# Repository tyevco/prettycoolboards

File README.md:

# prettycoolboards

**Docs site:** <https://tyevco.github.io/prettycoolboards/>

Open hardware boards designed as code. The schematics and PCBs are generated
from Python into KiCad 10, routed with Freerouting plus a grid router, and
gated by ERC, DRC and schematic parity before any fab output is written.
Enclosures and mechanics are in build123d.

## Boards

| Board | Status | |
|---|---|---|
| [PrettyCool Caliper](caliper/README.md) | rev A in design | 150 mm digital caliper: magnetic and capacitive sensing, ESP32-S3 with BLE + Wi-Fi, colour IPS, reading memory, go/no-go, USB-C |

## Repository layout

```
tools/        shared Python → KiCad generator toolchain (see tools/README.md)
caliper/      one folder per board: hardware/, firmware/, app/, docs/
.vitepress/   docs site (VitePress), published to GitHub Pages by .github/workflows/docs.yml
```

The hardware toolchain runs on Linux: KiCad 10 (`kicad-cli` + `pcbnew`), Java 21 +
Freerouting 2.1, ngspice and build123d. On Windows, run it in WSL.

```sh
npm ci && npm run docs:dev   # preview the docs site locally
```

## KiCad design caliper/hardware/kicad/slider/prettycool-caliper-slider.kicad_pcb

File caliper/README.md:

# PrettyCool Caliper

A 150 mm digital caliper that remembers its readings and sends them wirelessly.

> **Status (2026-11-10): rev A designed, not built.** Schematics captured (ERC clean, 2 waived); both boards laid
> out and routed (KiCad 10.0.8 DRC + schematic parity: 0 errors, 0 unconnected); both fab packages pass
> `release.py`, including the jlcplace placement gate (slider 107 rows, 0 red, 0 yellow); the mechanics pass the clash
> check against the routed board; the firmware builds for the ESP32-S3 and passes its host tests. Nothing has been
> fabricated, flashed, printed or measured, and no SPICE simulation has been run. Every figure here is a design
> target until the prototype passes [bring-up](docs/bringup.md).

| | |
|---|---|
| Sensing | AS5311 magnetic linear encoder over 2 mm-pole tape (0.488 µm internal resolution: the 1.95 µm quadrature count interpolated with the 12-bit SSI position), plus an experimental 8-phase capacitive scale on its own PCB, read side by side |
| Brains | ESP32-S3-MINI-1: BLE 5 and Wi-Fi |
| Display | 1.14 in colour IPS, landscape: big reading, live graph, go/no-go gauge, stats |
| Wireless | BLE HID keyboard (types the reading into any spreadsheet), a companion GATT app, a Wi-Fi web page, MQTT/HTTP push |
| Memory | Thousands of readings with timestamps and tolerance profiles; CSV export over USB, Wi-Fi or BLE |
| Smarts | Tolerance / go-no-go, min/max/mean/σ stats, 6-axis IMU (accelerometer + gyroscope): wake-on-pickup, auto-hold, orientation tracking; a compass (IIS2MDC magnetometer) as a reference that keeps the relative yaw from drifting: beside a steel beam it reads the local field, not north, and how well that works is unmeasured |
| Power | 135 mAh LiPo (501230 class, behind the board), USB-C charging (BQ25180), fuel gauge, buck-boost 3V3. Estimated ≈ 3 days per charge on a typical shop day (30 min measuring a day), ≈ 1 h 40 min of continuous measuring ([architecture §5](docs/architecture.md)); not measured |
| Body | Rev A: printed slider on a ground 20 × 4 mm flat-stock beam. Rev B: CNC-machined drawings. Slider housing 77 × 39 × 16 mm (slimmed from 77 × 52 × 16 on 2026-11-09) |

**[3D gallery](https://tyevco.github.io/prettycoolboards/caliper/gallery/):** rotate the assembly, the exploded
view, the housing on its own, the before/after slim-down and both circuit boards, plus the full render set.

## Documentation

| Document | Contents |
|---|---|
| [docs/architecture.md](docs/architecture.md) | System overview, decisions and the alternatives that were rejected, power budget |
| [hardware/design/SPEC.md](hardware/design/SPEC.md) | **Architecture of record**: boards, placement, power tree, pin map |
| [docs/electronics.md](docs/electronics.md) | Schematics, boards, ERC/DRC status, renders |
| [docs/mechanical.md](docs/mechanical.md) | Beam, slider housing, gibs, jaws; printed rev A and machined rev B |
| [docs/simulation.md](docs/simulation.md) | Placeholder: the SPICE checks of the power path and the capacitive front-end are not written or run yet |
| [docs/firmware.md](docs/firmware.md) | ESP-IDF firmware: sensing, UI, BLE, Wi-Fi, storage, power |
| [docs/app.md](docs/app.md) | Web Bluetooth companion page |
| [docs/assembly.md](docs/assembly.md) | Ordering (JLCPCB), sourcing, assembly |
| [docs/ordering.md](docs/ordering.md) | One-page order checklist: JLC options, panel, rough cost, off-board parts (prepared, nothing ordered) |
| [docs/bringup.md](docs/bringup.md) | The bring-up procedure B-0…B-17: test pads, supplies, meter points, expected values, the `bu` console checks; written, not run |

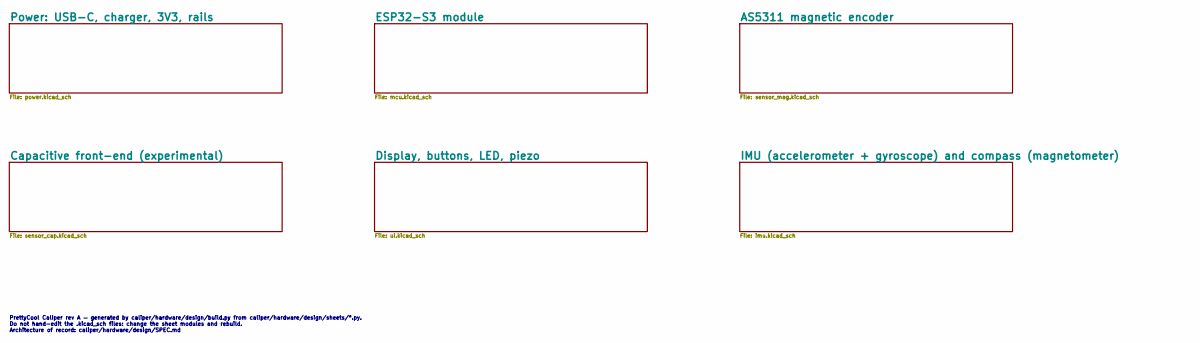
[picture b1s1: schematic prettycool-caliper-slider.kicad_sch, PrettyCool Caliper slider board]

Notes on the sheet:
PrettyCool Caliper rev A — generated by caliper/hardware/design/build.py from caliper/hardware/design/sheets/*.py. Do not hand-edit the .kicad_sch files: change the sheet modules and rebuild. Architecture of record: caliper/hardware/design/SPEC.md

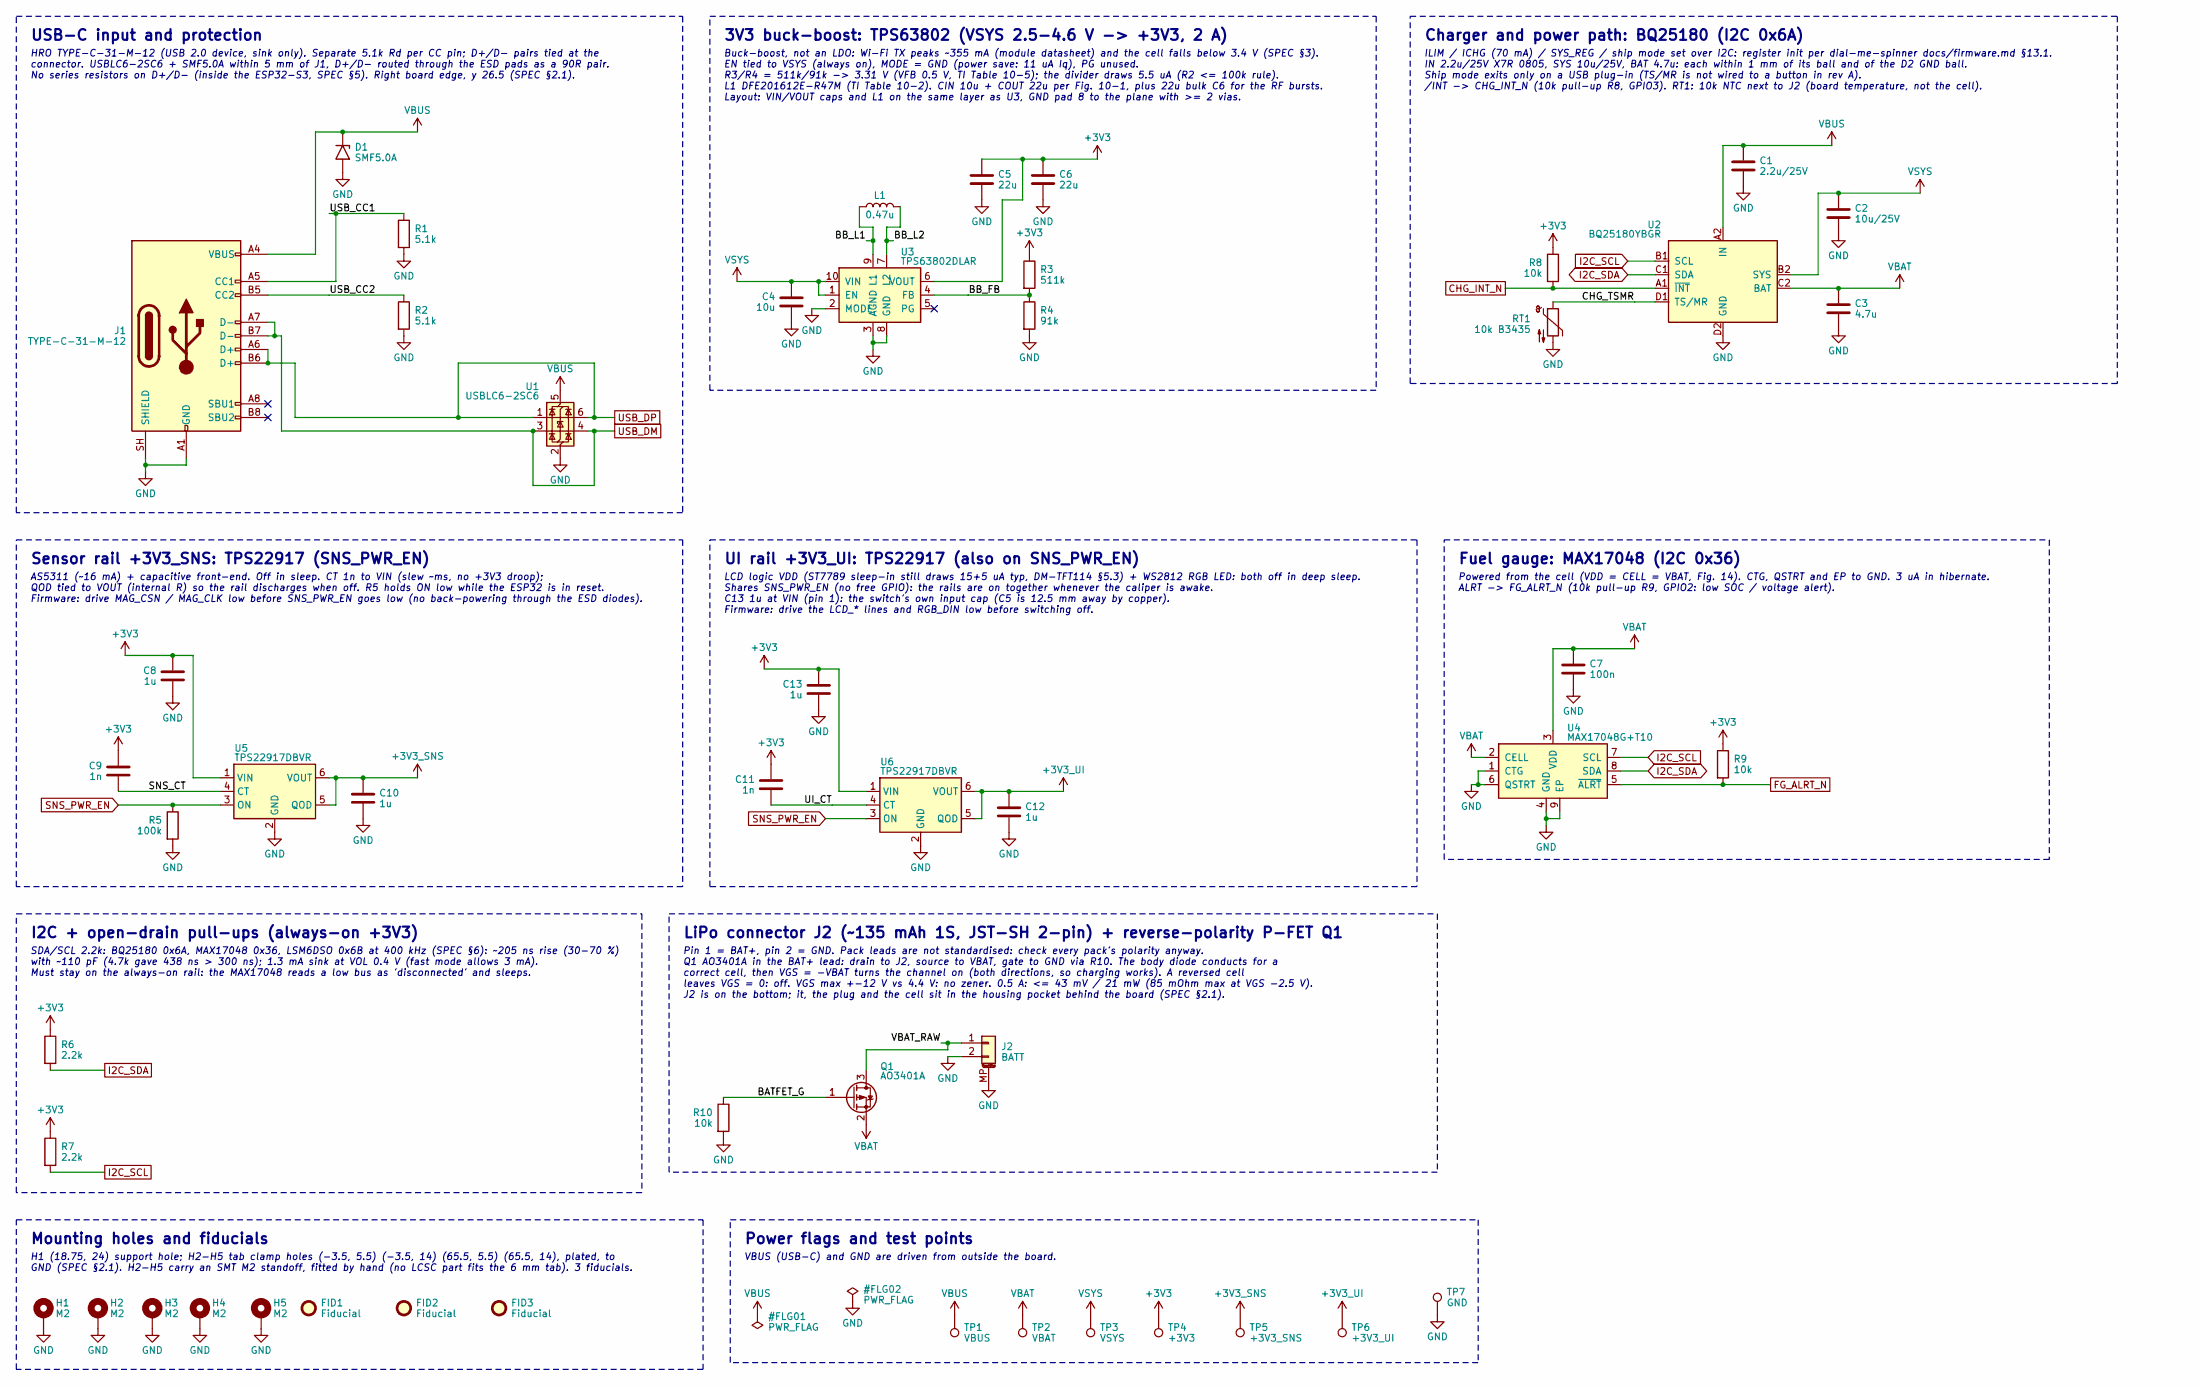
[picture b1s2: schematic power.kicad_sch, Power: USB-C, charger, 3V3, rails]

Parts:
C1: 2.2u/25V; C_0805_2012Metric; MPN CC0805KKX7R8BB225; LCSC C277470
C2: 10u/25V; C_0603_1608Metric; MPN CL10A106MA8NRNC; LCSC C96446
C3: 4.7u; C_0603_1608Metric; MPN CL10A475KO8NNNC; LCSC C19666
C4: 10u; C_0603_1608Metric; MPN CL10A106KP8NNNC; LCSC C19702
C5, C6: 22u; C_0603_1608Metric; MPN CL10A226MQ8NRNC; LCSC C59461
C7: 100n; C_0402_1005Metric; MPN CL05B104KO5NNNC; LCSC C1525
C8, C10, C12, C13: 1u; C_0402_1005Metric; MPN CL05A105KA5NQNC; LCSC C52923
C9, C11: 1n; C_0402_1005Metric; MPN 0402B102K500NT; LCSC C1523
D1: SMF5.0A; D_SMF; MPN SMF5.0A; LCSC C151296
FID1, FID2, FID3: Fiducial; Fiducial_1mm_Mask2mm
H1, H2, H3, H4, H5: M2; MountingHole_2.2mm_M2_Pad_Via
J1: TYPE-C-31-M-12; USB_C_Receptacle_HRO_TYPE-C-31-M-12; MPN TYPE-C-31-M-12; LCSC C165948
J2: BATT; JST_SH_SM02B-SRSS-TB_1x02-1MP_P1.00mm_Horizontal; MPN SM02B-SRSS-TB(LF)(SN); LCSC C160402
L1: 0.47u; L_Murata_DFE201610P; MPN DFE201612E-R47M=P2; LCSC C668312
Q1: AO3401A; SOT-23; MPN AO3401A; LCSC C15127
R1, R2: 5.1k; R_0402_1005Metric; MPN 0402WGF5101TCE; LCSC C25905
R3: 511k; R_0402_1005Metric; MPN 0402WGF5113TCE; LCSC C64042
R4: 91k; R_0402_1005Metric; MPN 0402WGF9102TCE; LCSC C4147
R5: 100k; R_0402_1005Metric; MPN 0402WGF1003TCE; LCSC C25741
R6, R7: 2.2k; R_0402_1005Metric; MPN 0402WGF2201TCE; LCSC C25879
R8, R9, R10: 10k; R_0402_1005Metric; MPN 0402WGF1002TCE; LCSC C25744
RT1: 10k B3435; R_0402_1005Metric; MPN NCP15XH103F03RC; LCSC C77131
TP1: VBUS; TestPoint_Pad_D1.0mm
TP2: VBAT; TestPoint_Pad_D1.0mm
TP3: VSYS; TestPoint_Pad_D1.0mm
TP4: +3V3; TestPoint_Pad_D1.0mm
TP5: +3V3_SNS; TestPoint_Pad_D1.0mm
TP6: +3V3_UI; TestPoint_Pad_D1.0mm
TP7: GND; TestPoint_Pad_D1.0mm
U1: USBLC6-2SC6; SOT-23-6; MPN USBLC6-2SC6; LCSC C7519
U2: BQ25180YBGR; Texas_DSBGA-8_1.04x1.59mm_Layout2x4_P0.4mm_YBG0008; MPN BQ25180YBGR; LCSC C3682423
U3: TPS63802DLAR; Texas_DLA0010A_VSON-HR-10_2x3mm_P0.5mm; MPN TPS63802DLAR; LCSC C2845237
U4: MAX17048G+T10; TDFN-8-1EP_2x2mm_P0.5mm_EP0.8x1.2mm; MPN MAX17048G+T10; LCSC C2682616
U5, U6: TPS22917DBVR; SOT-23-6; MPN TPS22917DBVR; LCSC C2681320

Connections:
+3V3: C5.1, C6.1, C8.1, C9.2, C11.2, C13.1, R3.1, R6.1, R7.1, R8.1, R9.1, TP4.1, U3.6 (VOUT), U5.1 (VIN), U6.1 (VIN); also elsewhere on the board
+3V3_SNS: C10.1, TP5.1, U5.5 (QOD), U5.6 (VOUT); also elsewhere on the board
+3V3_UI: C12.1, TP6.1, U6.5 (QOD), U6.6 (VOUT); also elsewhere on the board
/Power: USB-C, charger, 3V3, rails/BATFET_G: Q1.1 (G), R10.1
/Power: USB-C, charger, 3V3, rails/BB_FB: R3.2, R4.1, U3.4 (FB)
/Power: USB-C, charger, 3V3, rails/BB_L1: L1.1, U3.9 (L1)
/Power: USB-C, charger, 3V3, rails/BB_L2: L1.2, U3.7 (L2)
/Power: USB-C, charger, 3V3, rails/CHG_TSMR: RT1.1, U2.D1 (TS/MR)
/Power: USB-C, charger, 3V3, rails/SNS_CT: C9.1, U5.4 (CT)
/Power: USB-C, charger, 3V3, rails/UI_CT: C11.1, U6.4 (CT)
/Power: USB-C, charger, 3V3, rails/USB_CC1: J1.A5 (CC1), R1.1
/Power: USB-C, charger, 3V3, rails/USB_CC2: J1.B5 (CC2), R2.1
/Power: USB-C, charger, 3V3, rails/VBAT_RAW: J2.1, Q1.3 (D)
CHG_INT_N: R8.2, U2.A1 (~INT); also elsewhere on the board
FG_ALRT_N: R9.2, U4.5 (~ALRT); also elsewhere on the board
GND: C1.2, C2.2, C3.2, C4.2, C5.2, C6.2, C7.2, C8.2, C10.2, C12.2, C13.2, D1.2 (A2), H1.1, H2.1, H3.1, H4.1, H5.1, J1.A1 (GND), J1.A12 (GND), J1.B1 (GND), J1.B12 (GND), J1.SH (SHIELD), J2.2, J2.MP (MountPin), R1.2, R2.2, R4.2, R5.2, R10.2, RT1.2, TP7.1, U1.2 (GND), U2.D2 (GND), U3.2 (MODE), U3.3 (AGND), U3.8 (GND), U4.1 (CTG), U4.4 (GND), U4.6 (QSTRT), U4.9 (EP), U5.2 (GND), U6.2 (GND); also elsewhere on the board
I2C_SCL: R7.2, U2.B1 (SCL), U4.7 (SCL); also elsewhere on the board
I2C_SDA: R6.2, U2.C1 (SDA), U4.8 (SDA); also elsewhere on the board
SNS_PWR_EN: R5.1, U5.3 (ON), U6.3 (ON); also elsewhere on the board
USB_DM: J1.A7 (D-), J1.B7 (D-), U1.3 (I/O2), U1.4 (I/O2); also elsewhere on the board
USB_DP: J1.A6 (D+), J1.B6 (D+), U1.1 (I/O1), U1.6 (I/O1); also elsewhere on the board
VBAT: C3.1, C7.1, Q1.2 (S), TP2.1, U2.C2 (BAT), U4.2 (CELL), U4.3 (VDD)
VBUS: C1.1, D1.1 (A1), J1.A4 (VBUS), J1.A9 (VBUS), J1.B4 (VBUS), J1.B9 (VBUS), TP1.1, U1.5 (VBUS), U2.A2 (IN)
VSYS: C2.1, C4.1, TP3.1, U2.B2 (SYS), U3.1 (EN), U3.10 (VIN)

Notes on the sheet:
USB-C input and protection
HRO TYPE-C-31-M-12 (USB 2.0 device, sink only). Separate 5.1k Rd per CC pin; D+/D- pairs tied at the connector. USBLC6-2SC6 + SMF5.0A within 5 mm of J1, D+/D- routed through the ESD pads as a 90R pair. No series resistors on D+/D- (inside the ESP32-S3, SPEC §5). Right board edge, y 26.5 (SPEC §2.1).
Charger and power path: BQ25180 (I2C 0x6A)
ILIM / ICHG (70 mA) / SYS_REG / ship mode set over I2C: register init per dial-me-spinner docs/firmware.md §13.1. IN 2.2u/25V X7R 0805, SYS 10u/25V, BAT 4.7u: each within 1 mm of its ball and of the D2 GND ball. Ship mode exits only on a USB plug-in (TS/MR is not wired to a button in rev A). /INT -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
LiPo connector J2 (~135 mAh 1S, JST-SH 2-pin) + reverse-polarity P-FET Q1
Pin 1 = BAT+, pin 2 = GND. Pack leads are not standardised: check every pack's polarity anyway. Q1 AO3401A in the BAT+ lead: drain to J2, source to VBAT, gate to GND via R10. The body diode conducts for a correct cell, then VGS = -VBAT turns the channel on (both directions, so charging works). A re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
3V3 buck-boost: TPS63802 (VSYS 2.5-4.6 V -> +3V3, 2 A)
Buck-boost, not an LDO: Wi-Fi TX peaks ~355 mA (module datasheet) and the cell falls below 3.4 V (SPEC §3). EN tied to VSYS (always on), MODE = GND (power save: 11 uA Iq), PG unused. R3/R4 = 511k/91k -> 3.31 V (VFB 0.5 V, TI Table 10-5); the divider draws 5.5 uA (R2 <= 100k rule). L1 DFE201612E-R47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
Fuel gauge: MAX17048 (I2C 0x36)
Powered from the cell (VDD = CELL = VBAT, Fig. 14). CTG, QSTRT and EP to GND. 3 uA in hibernate. ALRT -> FG_ALRT_N (10k pull-up R9, GPIO2: low SOC / voltage alert).
Sensor rail +3V3_SNS: TPS22917 (SNS_PWR_EN)
AS5311 (~16 mA) + capacitive front-end. Off in sleep. CT 1n to VIN (slew ~ms, no +3V3 droop); QOD tied to VOUT (internal R) so the rail discharges when off. R5 holds ON low while the ESP32 is in reset. Firmware: drive MAG_CSN / MAG_CLK low before SNS_PWR_EN goes low (no back-powering through the ES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
UI rail +3V3_UI: TPS22917 (also on SNS_PWR_EN)
LCD logic VDD (ST7789 sleep-in still draws 15+5 uA typ, DM-TFT114 §5.3) + WS2812 RGB LED: both off in deep sleep. Shares SNS_PWR_EN (no free GPIO): the rails are on together whenever the caliper is awake. C13 1u at VIN (pin 1): the switch's own input cap (C5 is 12.5 mm away by copper). Firmware: dr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
I2C + open-drain pull-ups (always-on +3V3)
SDA/SCL 2.2k: BQ25180 0x6A, MAX17048 0x36, LSM6DSO 0x6B at 400 kHz (SPEC §6): ~205 ns rise (30-70 %) with ~110 pF (4.7k gave 438 ns > 300 ns); 1.3 mA sink at VOL 0.4 V (fast mode allows 3 mA). Must stay on the always-on rail: the MAX17048 reads a low bus as 'disconnected' and sleeps.
Mounting holes and fiducials
H1 (18.75, 24) support hole; H2-H5 tab clamp holes (-3.5, 5.5) (-3.5, 14) (65.5, 5.5) (65.5, 14), plated, to GND (SPEC §2.1). H2-H5 carry an SMT M2 standoff, fitted by hand (no LCSC part fits the 6 mm tab). 3 fiducials.
Power flags and test points
VBUS (USB-C) and GND are driven from outside the board.

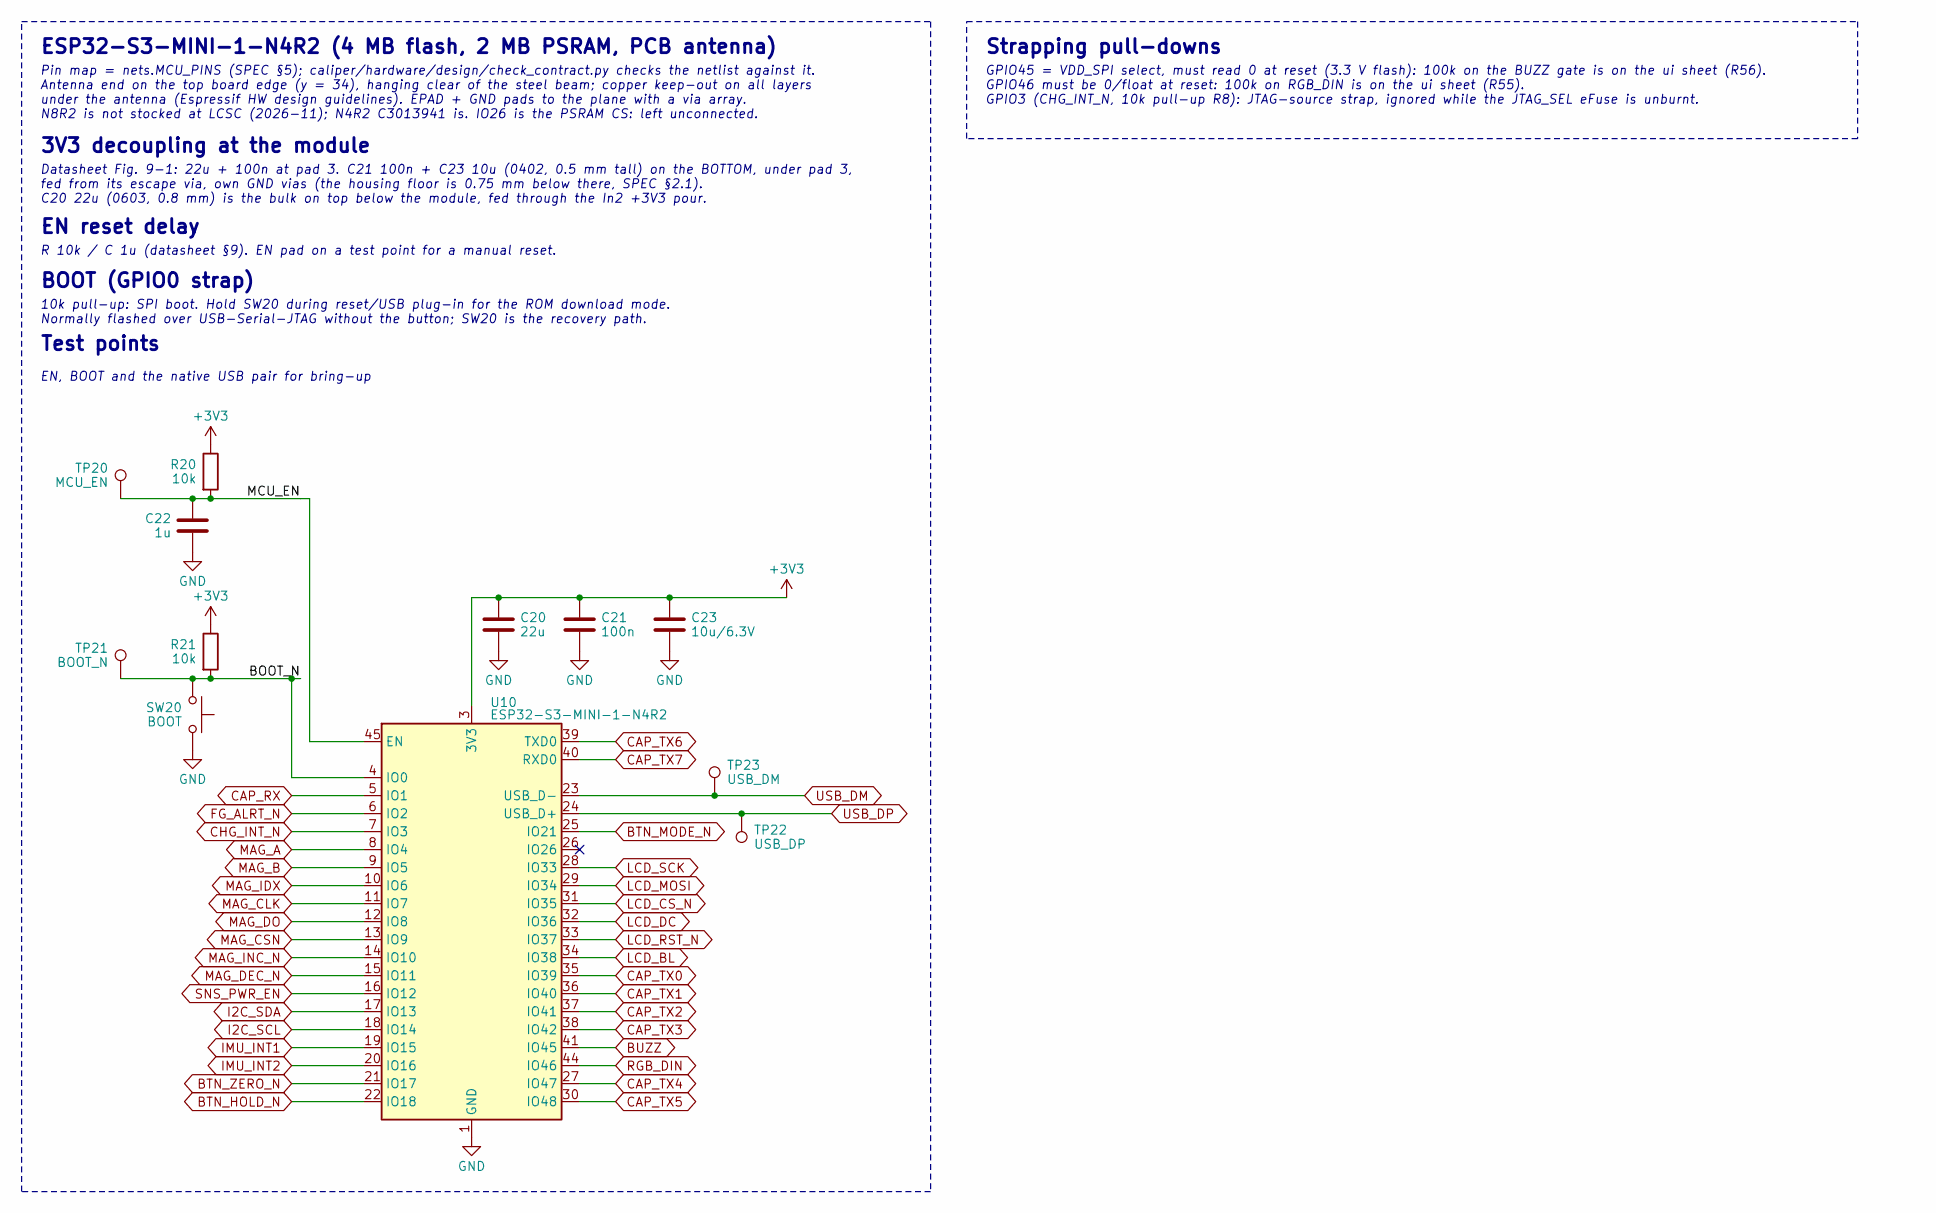
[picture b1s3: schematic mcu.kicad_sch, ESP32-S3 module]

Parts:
C20: 22u; C_0603_1608Metric; MPN CL10A226MQ8NRNC; LCSC C59461
C21: 100n; C_0402_1005Metric; MPN CL05B104KO5NNNC; LCSC C1525
C22: 1u; C_0402_1005Metric; MPN CL05A105KA5NQNC; LCSC C52923
C23: 10u/6.3V; C_0402_1005Metric; MPN CL05A106MQ5NUNC; LCSC C15525
R20, R21: 10k; R_0402_1005Metric; MPN 0402WGF1002TCE; LCSC C25744
SW20: BOOT; SW_SPST_TS-1088-xR020; MPN TS-1088-AR02016; LCSC C720477
TP20: MCU_EN; TestPoint_Pad_D1.0mm
TP21: BOOT_N; TestPoint_Pad_D1.0mm
TP22: USB_DP; TestPoint_Pad_D1.0mm
TP23: USB_DM; TestPoint_Pad_D1.0mm
U10: ESP32-S3-MINI-1-N4R2; ESP32-S2-MINI-1; MPN ESP32-S3-MINI-1-N4R2; LCSC C3013941

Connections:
+3V3: C20.1, C21.1, C23.1, R20.1, R21.1, U10.3 (3V3); also elsewhere on the board
/ESP32-S3 module/BOOT_N: R21.2, SW20.1, TP21.1, U10.4 (IO0)
/ESP32-S3 module/MCU_EN: C22.1, R20.2, TP20.1, U10.45 (EN)
BTN_HOLD_N: U10.22 (IO18); also elsewhere on the board
BTN_MODE_N: U10.25 (IO21); also elsewhere on the board
BTN_ZERO_N: U10.21 (IO17); also elsewhere on the board
BUZZ: U10.41 (IO45); also elsewhere on the board
CAP_RX: U10.5 (IO1); also elsewhere on the board
CAP_TX0: U10.35 (IO39); also elsewhere on the board
CAP_TX1: U10.36 (IO40); also elsewhere on the board
CAP_TX2: U10.37 (IO41); also elsewhere on the board
CAP_TX3: U10.38 (IO42); also elsewhere on the board
CAP_TX4: U10.27 (IO47); also elsewhere on the board
CAP_TX5: U10.30 (IO48); also elsewhere on the board
CAP_TX6: U10.39 (TXD0); also elsewhere on the board
CAP_TX7: U10.40 (RXD0); also elsewhere on the board
CHG_INT_N: U10.7 (IO3); also elsewhere on the board
FG_ALRT_N: U10.6 (IO2); also elsewhere on the board
GND: C20.2, C21.2, C22.2, C23.2, SW20.2, U10.1 (GND), U10.2 (GND), U10.42 (GND), U10.43 (GND), U10.46 (GND), U10.47 (GND), U10.48 (GND), U10.49 (GND), U10.50 (GND), U10.51 (GND), U10.52 (GND), U10.53 (GND), U10.54 (GND), U10.55 (GND), U10.56 (GND), U10.57 (GND), U10.58 (GND), U10.59 (GND), U10.60 (GND), U10.61 (GND), U10.62 (GND), U10.63 (GND), U10.64 (GND), U10.65 (GND); also elsewhere on the board
I2C_SCL: U10.18 (IO14); also elsewhere on the board
I2C_SDA: U10.17 (IO13); also elsewhere on the board
IMU_INT1: U10.19 (IO15); also elsewhere on the board
IMU_INT2: U10.20 (IO16); also elsewhere on the board
LCD_BL: U10.34 (IO38); also elsewhere on the board
LCD_CS_N: U10.31 (IO35); also elsewhere on the board
LCD_DC: U10.32 (IO36); also elsewhere on the board
LCD_MOSI: U10.29 (IO34); also elsewhere on the board
LCD_RST_N: U10.33 (IO37); also elsewhere on the board
LCD_SCK: U10.28 (IO33); also elsewhere on the board
MAG_A: U10.8 (IO4); also elsewhere on the board
MAG_B: U10.9 (IO5); also elsewhere on the board
MAG_CLK: U10.11 (IO7); also elsewhere on the board
MAG_CSN: U10.13 (IO9); also elsewhere on the board
MAG_DEC_N: U10.15 (IO11); also elsewhere on the board
MAG_DO: U10.12 (IO8); also elsewhere on the board
MAG_IDX: U10.10 (IO6); also elsewhere on the board
MAG_INC_N: U10.14 (IO10); also elsewhere on the board
RGB_DIN: U10.44 (IO46); also elsewhere on the board
SNS_PWR_EN: U10.16 (IO12); also elsewhere on the board
USB_DM: TP23.1, U10.23 (USB_D-); also elsewhere on the board
USB_DP: TP22.1, U10.24 (USB_D+); also elsewhere on the board

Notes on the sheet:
ESP32-S3-MINI-1-N4R2 (4 MB flash, 2 MB PSRAM, PCB antenna)
Pin map = nets.MCU_PINS (SPEC §5); caliper/hardware/design/check_contract.py checks the netlist against it. Antenna end on the top board edge (y = 34), hanging clear of the steel beam; copper keep-out on all layers under the antenna (Espressif HW design guidelines). EPAD + GND pads to the plane wit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
3V3 decoupling at the module
Datasheet Fig. 9-1: 22u + 100n at pad 3. C21 100n + C23 10u (0402, 0.5 mm tall) on the BOTTOM, under pad 3, fed from its escape via, own GND vias (the housing floor is 0.75 mm below there, SPEC §2.1). C20 22u (0603, 0.8 mm) is the bulk on top below the module, fed through the In2 +3V3 pour.
EN reset delay
R 10k / C 1u (datasheet §9). EN pad on a test point for a manual reset.
BOOT (GPIO0 strap)
10k pull-up: SPI boot. Hold SW20 during reset/USB plug-in for the ROM download mode. Normally flashed over USB-Serial-JTAG without the button; SW20 is the recovery path.
Test points
EN, BOOT and the native USB pair for bring-up
Strapping pull-downs
GPIO45 = VDD_SPI select, must read 0 at reset (3.3 V flash): 100k on the BUZZ gate is on the ui sheet (R56). GPIO46 must be 0/float at reset: 100k on RGB_DIN is on the ui sheet (R55). GPIO3 (CHG_INT_N, 10k pull-up R8): JTAG-source strap, ignored while the JTAG_SEL eFuse is unburnt.

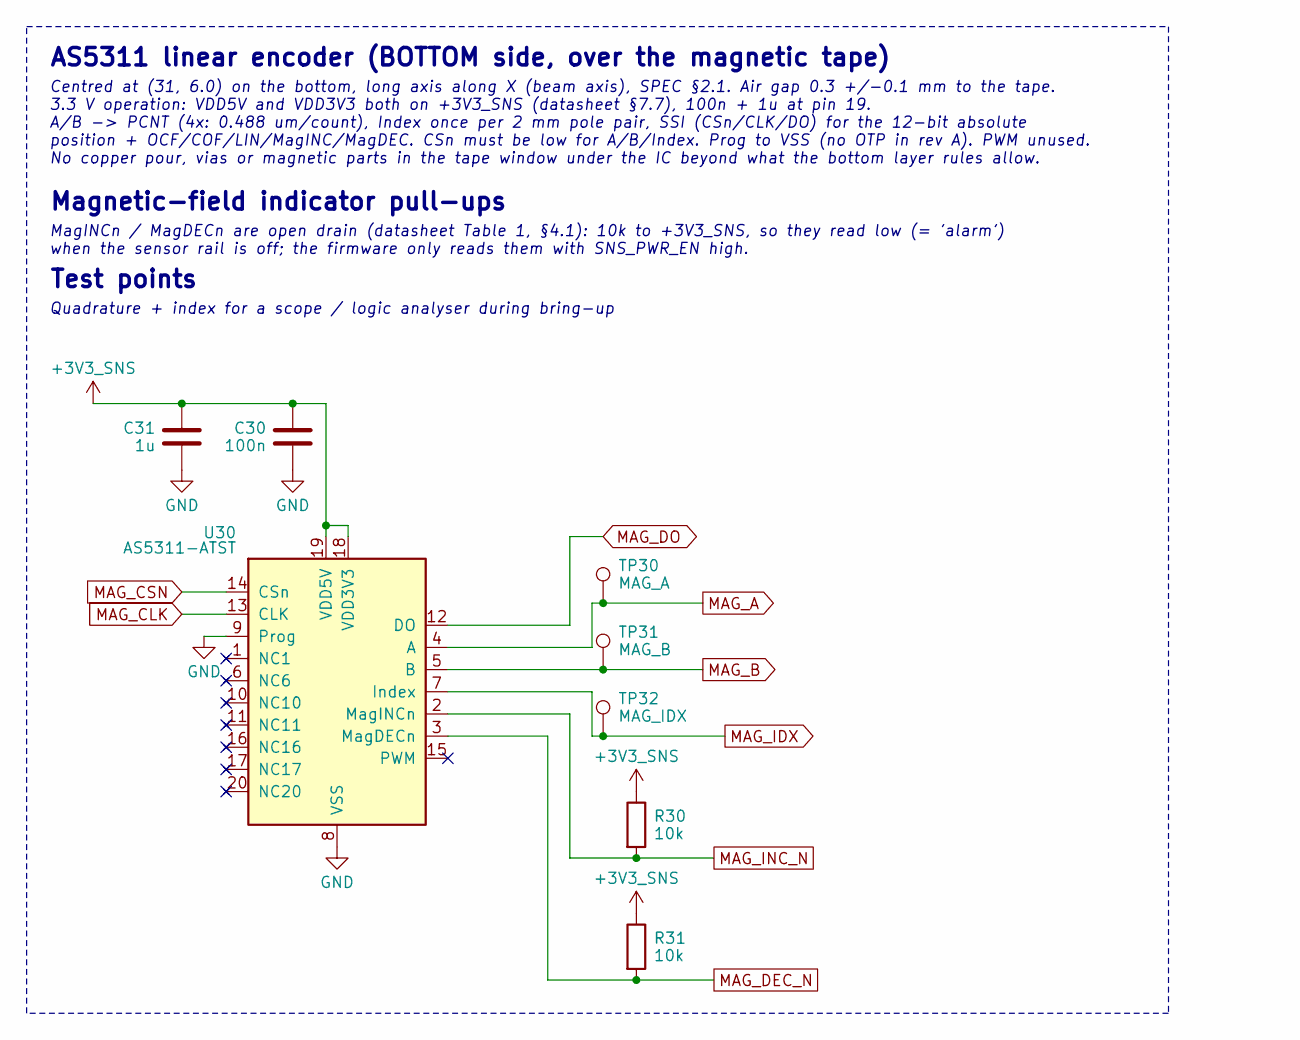
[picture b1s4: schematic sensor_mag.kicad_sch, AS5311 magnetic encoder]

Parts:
C30: 100n; C_0402_1005Metric; MPN CL05B104KO5NNNC; LCSC C1525
C31: 1u; C_0402_1005Metric; MPN CL05A105KA5NQNC; LCSC C52923
R30, R31: 10k; R_0402_1005Metric; MPN 0402WGF1002TCE; LCSC C25744
TP30: MAG_A; TestPoint_Pad_D1.0mm
TP31: MAG_B; TestPoint_Pad_D1.0mm
TP32: MAG_IDX; TestPoint_Pad_D1.0mm
U30: AS5311-ATST; TSSOP-20_4.4x6.5mm_P0.65mm; MPN AS5311-ATST; LCSC C22459687

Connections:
+3V3_SNS: C30.1, C31.1, R30.1, R31.1, U30.18 (VDD3V3), U30.19 (VDD5V); also elsewhere on the board
GND: C30.2, C31.2, U30.8 (VSS), U30.9 (Prog); also elsewhere on the board
MAG_A: TP30.1, U30.4 (A); also elsewhere on the board
MAG_B: TP31.1, U30.5 (B); also elsewhere on the board
MAG_CLK: U30.13 (CLK); also elsewhere on the board
MAG_CSN: U30.14 (CSn); also elsewhere on the board
MAG_DEC_N: R31.2, U30.3 (MagDECn); also elsewhere on the board
MAG_DO: U30.12 (DO); also elsewhere on the board
MAG_IDX: TP32.1, U30.7 (Index); also elsewhere on the board
MAG_INC_N: R30.2, U30.2 (MagINCn); also elsewhere on the board

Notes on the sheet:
AS5311 linear encoder (BOTTOM side, over the magnetic tape)
Centred at (31, 6.0) on the bottom, long axis along X (beam axis), SPEC §2.1. Air gap 0.3 +/-0.1 mm to the tape. 3.3 V operation: VDD5V and VDD3V3 both on +3V3_SNS (datasheet §7.7), 100n + 1u at pin 19. A/B -> PCNT (4x: 0.488 um/count), Index once per 2 mm pole pair, SSI (CSn/CLK/DO) for the 12-bit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
Magnetic-field indicator pull-ups
MagINCn / MagDECn are open drain (datasheet Table 1, §4.1): 10k to +3V3_SNS, so they read low (= 'alarm') when the sensor rail is off; the firmware only reads them with SNS_PWR_EN high.
Test points
Quadrature + index for a scope / logic analyser during bring-up

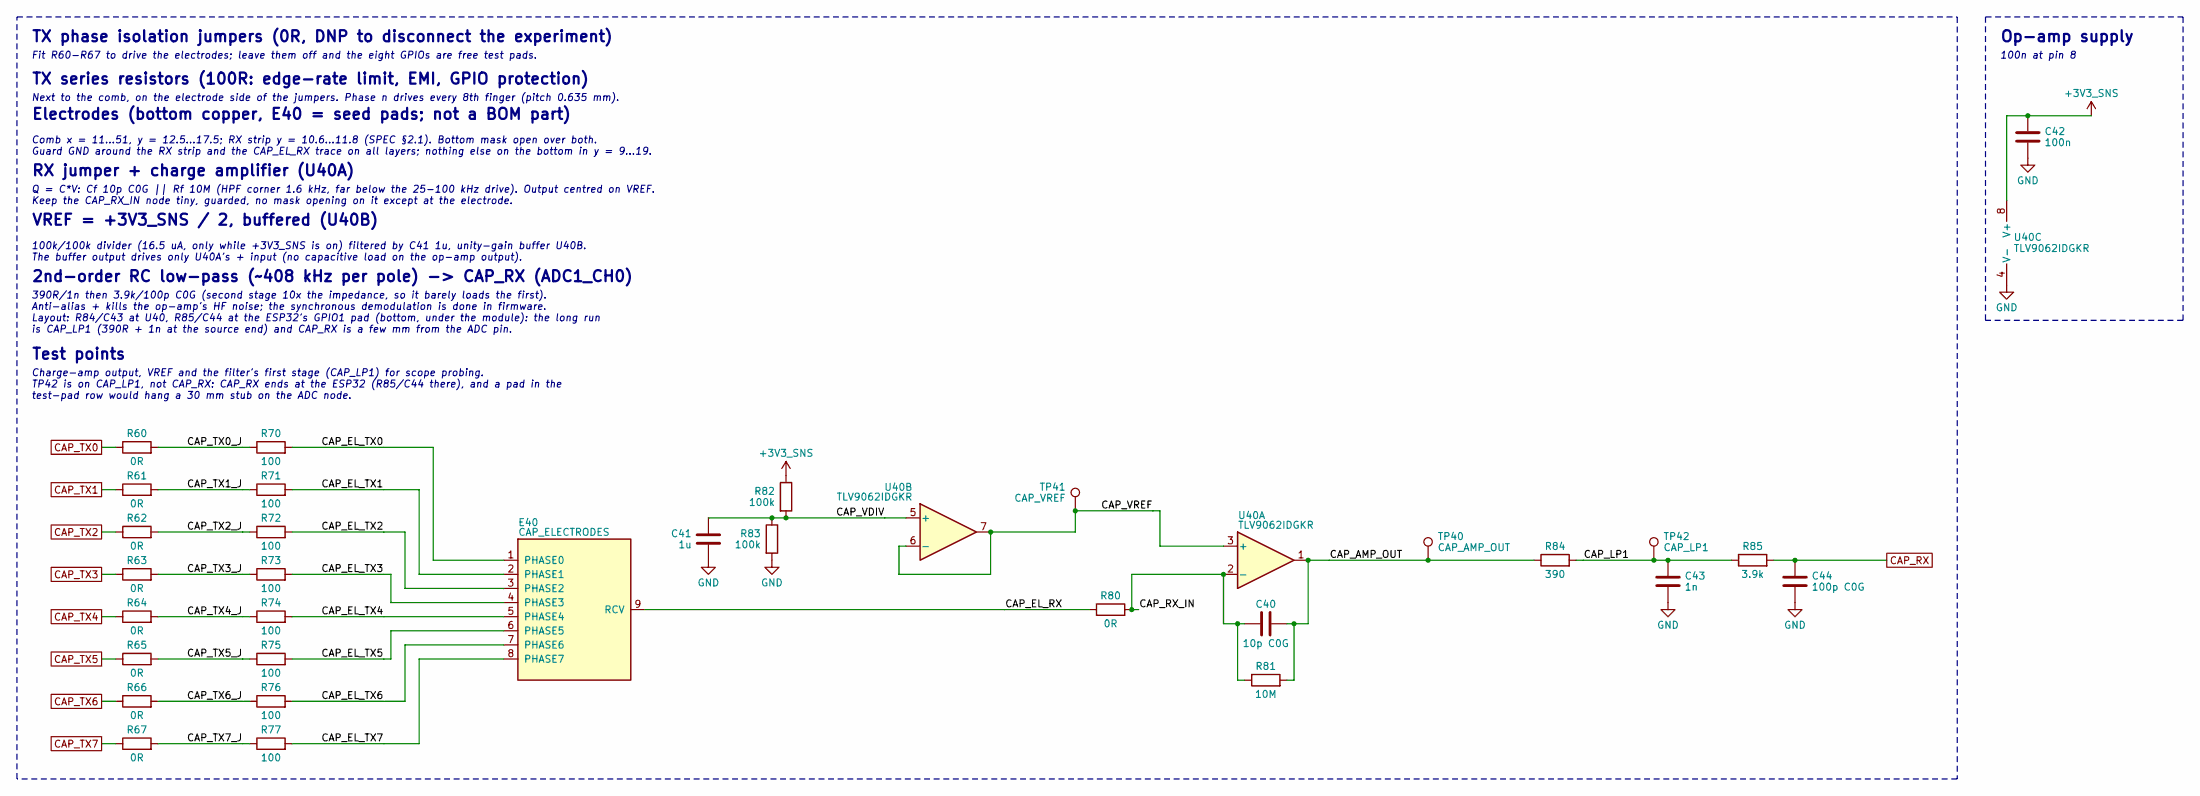
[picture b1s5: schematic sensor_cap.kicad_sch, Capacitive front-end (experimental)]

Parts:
C40: 10p C0G; C_0402_1005Metric; MPN 0402CG100J500NT; LCSC C1545
C41: 1u; C_0402_1005Metric; MPN CL05A105KA5NQNC; LCSC C52923
C42: 100n; C_0402_1005Metric; MPN CL05B104KO5NNNC; LCSC C1525
C43: 1n; C_0402_1005Metric; MPN 0402B102K500NT; LCSC C1523
C44: 100p C0G; C_0402_1005Metric; MPN 0402CG101J500NT; LCSC C1546
E40: CAP_ELECTRODES; Caliper_CapTX_Electrode_Seed_8Phase_P0.635mm
R60, R61, R62, R63, R64, R65, R66, R67, R80: 0R; R_0402_1005Metric; MPN 0402WGF0000TCE; LCSC C17168
R70, R71, R72, R73, R74, R75, R76, R77: 100; R_0402_1005Metric; MPN 0402WGF1000TCE; LCSC C25076
R81: 10M; R_0402_1005Metric; MPN 0402WGF1005TCE; LCSC C26082
R82, R83: 100k; R_0402_1005Metric; MPN 0402WGF1003TCE; LCSC C25741
R84: 390; R_0402_1005Metric; MPN 0402WGF3900TCE; LCSC C25109
R85: 3.9k; R_0402_1005Metric; MPN 0402WGF3901TCE; LCSC C51721
TP40: CAP_AMP_OUT; TestPoint_Pad_D1.0mm
TP41: CAP_VREF; TestPoint_Pad_D1.0mm
TP42: CAP_LP1; TestPoint_Pad_D1.0mm
U40: TLV9062IDGKR; VSSOP-8_3x3mm_P0.65mm; MPN TLV9062IDGKR; LCSC C398356

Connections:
+3V3_SNS: C42.1, R82.1, U40.8 (V+); also elsewhere on the board
/Capacitive front-end (experimental)/CAP_AMP_OUT: C40.2, R81.2, R84.1, TP40.1, U40.1
/Capacitive front-end (experimental)/CAP_EL_RX: E40.9 (RCV), R80.1
/Capacitive front-end (experimental)/CAP_EL_TX0: E40.1 (PHASE0), R70.2
/Capacitive front-end (experimental)/CAP_EL_TX1: E40.2 (PHASE1), R71.2
/Capacitive front-end (experimental)/CAP_EL_TX2: E40.3 (PHASE2), R72.2
/Capacitive front-end (experimental)/CAP_EL_TX3: E40.4 (PHASE3), R73.2
/Capacitive front-end (experimental)/CAP_EL_TX4: E40.5 (PHASE4), R74.2
/Capacitive front-end (experimental)/CAP_EL_TX5: E40.6 (PHASE5), R75.2
/Capacitive front-end (experimental)/CAP_EL_TX6: E40.7 (PHASE6), R76.2
/Capacitive front-end (experimental)/CAP_EL_TX7: E40.8 (PHASE7), R77.2
/Capacitive front-end (experimental)/CAP_LP1: C43.1, R84.2, R85.1, TP42.1
/Capacitive front-end (experimental)/CAP_RX_IN: C40.1, R80.2, R81.1, U40.2 (-)
/Capacitive front-end (experimental)/CAP_TX0_J: R60.2, R70.1
/Capacitive front-end (experimental)/CAP_TX1_J: R61.2, R71.1
/Capacitive front-end (experimental)/CAP_TX2_J: R62.2, R72.1
/Capacitive front-end (experimental)/CAP_TX3_J: R63.2, R73.1
/Capacitive front-end (experimental)/CAP_TX4_J: R64.2, R74.1
/Capacitive front-end (experimental)/CAP_TX5_J: R65.2, R75.1
/Capacitive front-end (experimental)/CAP_TX6_J: R66.2, R76.1
/Capacitive front-end (experimental)/CAP_TX7_J: R67.2, R77.1
/Capacitive front-end (experimental)/CAP_VDIV: C41.1, R82.2, R83.1, U40.5 (+)
/Capacitive front-end (experimental)/CAP_VREF: TP41.1, U40.3 (+), U40.6 (-), U40.7
CAP_RX: C44.1, R85.2; also elsewhere on the board
CAP_TX0: R60.1; also elsewhere on the board
CAP_TX1: R61.1; also elsewhere on the board
CAP_TX2: R62.1; also elsewhere on the board
CAP_TX3: R63.1; also elsewhere on the board
CAP_TX4: R64.1; also elsewhere on the board
CAP_TX5: R65.1; also elsewhere on the board
CAP_TX6: R66.1; also elsewhere on the board
CAP_TX7: R67.1; also elsewhere on the board
GND: C41.2, C42.2, C43.2, C44.2, R83.2, U40.4 (V-); also elsewhere on the board

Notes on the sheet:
TX phase isolation jumpers (0R, DNP to disconnect the experiment)
Fit R60-R67 to drive the electrodes; leave them off and the eight GPIOs are free test pads.
TX series resistors (100R: edge-rate limit, EMI, GPIO protection)
Next to the comb, on the electrode side of the jumpers. Phase n drives every 8th finger (pitch 0.635 mm).
Electrodes (bottom copper, E40 = seed pads; not a BOM part)
Comb x = 11...51, y = 12.5...17.5; RX strip y = 10.6...11.8 (SPEC §2.1). Bottom mask open over both. Guard GND around the RX strip and the CAP_EL_RX trace on all layers; nothing else on the bottom in y = 9...19.
RX jumper + charge amplifier (U40A)
Q = C*V: Cf 10p C0G || Rf 10M (HPF corner 1.6 kHz, far below the 25-100 kHz drive). Output centred on VREF. Keep the CAP_RX_IN node tiny, guarded, no mask opening on it except at the electrode.
VREF = +3V3_SNS / 2, buffered (U40B)
100k/100k divider (16.5 uA, only while +3V3_SNS is on) filtered by C41 1u, unity-gain buffer U40B. The buffer output drives only U40A's + input (no capacitive load on the op-amp output).
2nd-order RC low-pass (~408 kHz per pole) -> CAP_RX (ADC1_CH0)
390R/1n then 3.9k/100p C0G (second stage 10x the impedance, so it barely loads the first). Anti-alias + kills the op-amp's HF noise; the synchronous demodulation is done in firmware. Layout: R84/C43 at U40, R85/C44 at the ESP32's GPIO1 pad (bottom, under the module): the long run is CAP_LP1 (390R +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
Test points
Charge-amp output, VREF and the filter's first stage (CAP_LP1) for scope probing. TP42 is on CAP_LP1, not CAP_RX: CAP_RX ends at the ESP32 (R85/C44 there), and a pad in the test-pad row would hang a 30 mm stub on the ADC node.
Op-amp supply
100n at pin 8
